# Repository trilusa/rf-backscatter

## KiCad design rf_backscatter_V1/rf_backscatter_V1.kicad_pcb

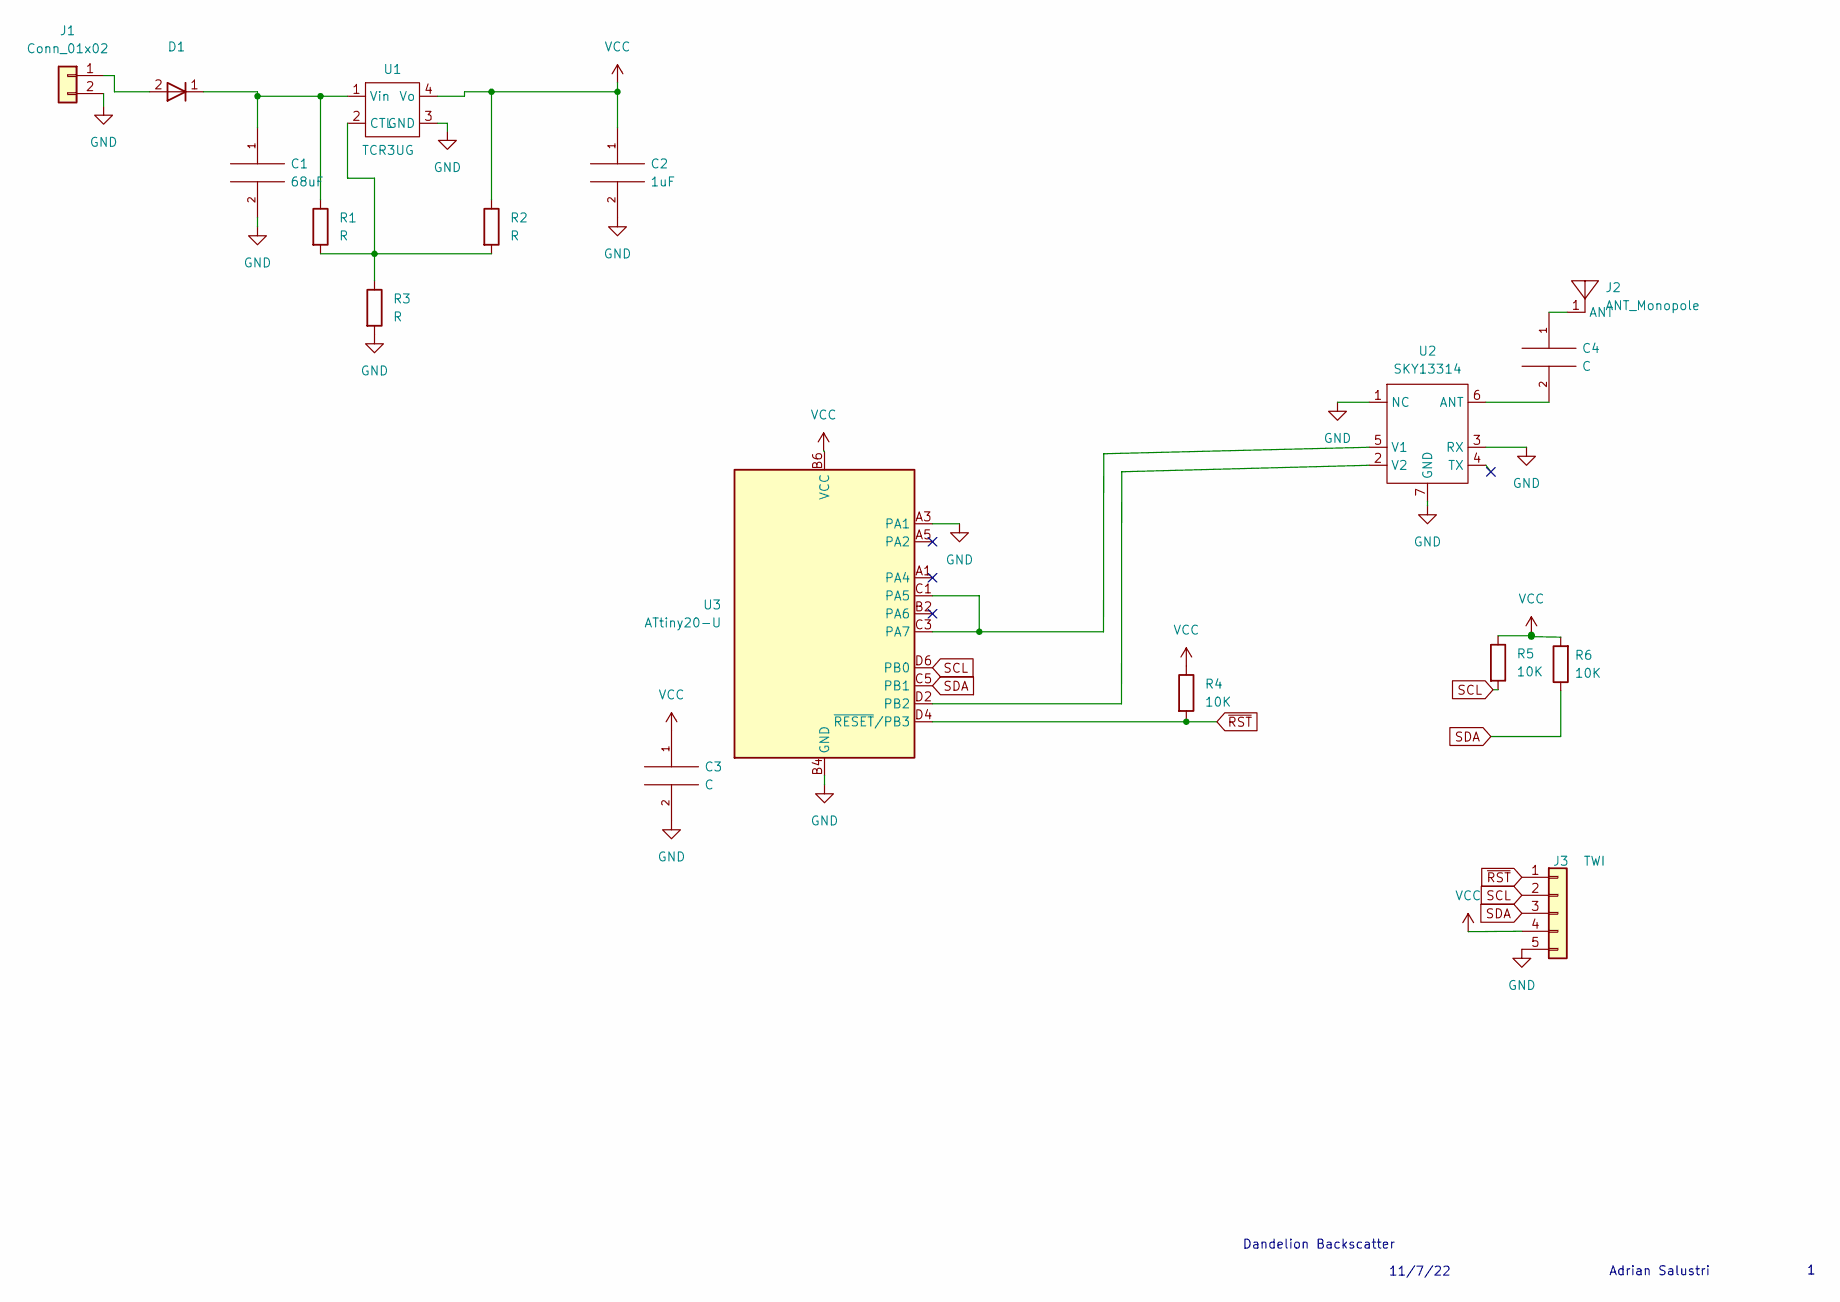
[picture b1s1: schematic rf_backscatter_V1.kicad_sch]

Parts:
C1: 68uF; C_0603_1608Metric_Pad1.08x0.95mm_HandSolder
C2: 1uF; C_0402_1005Metric_Pad0.74x0.62mm_HandSolder
C3, C4: C; C_0402_1005Metric_Pad0.74x0.62mm_HandSolder
D1: D; SOD882
J1: Conn_01x02; Dandelion_PVcell_connector
J2: ANT_Monopole; monopole_wire_antenna
J3: TWI; ATtiny20_TPI-I2C-HDR
R1, R2, R3: R; R_0402_1005Metric_Pad0.72x0.64mm_HandSolder
R4, R5, R6: 10K; R_0402_1005Metric
U1: TCR3UG
U2: SKY13314; SKY13314-374LF
U3: ATtiny20-U; WLCSP-12_1.403x1.555mm_P0.4mm_Stagger

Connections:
GND: C1.2, C2.2, C3.2, J1.2, J3.5, R3.2, U1.3 (GND), U2.1 (NC), U2.3 (RX), U2.7 (GND), U3.A3 (PA1), U3.B4 (GND)
unnamed: C1.1, D1.1 (K), R1.1, U1.1 (Vin)
unnamed: C4.1, J2.1 (ANT)
unnamed: C4.2, U2.6 (ANT)
unnamed: D1.2 (A), J1.1
unnamed: R1.2, R2.2, R3.1, U1.2 (CTL)
unnamed: U2.2 (V2), U3.D2 (PB2)
unnamed: U2.5 (V1), U3.C1 (PA5), U3.C3 (PA7)
SCL: J3.2, R5.2, U3.D6 (PB0)
SDA: J3.3, R6.1, U3.C5 (PB1)
VCC: C2.1, C3.1, J3.4, R2.1, R4.1, R5.1, R6.2, U1.4 (Vo), U3.B6 (VCC)
~RST: J3.1, R4.2, U3.D4 (~RESET/PB3)

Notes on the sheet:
Dandelion Backscatter
11/7/22
Adrian Salustri

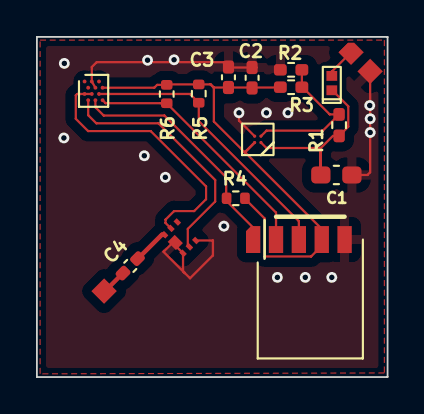
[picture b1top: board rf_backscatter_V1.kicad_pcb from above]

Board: 2 copper layers, 19.5 x 18.9 mm, 17 parts (0 on the bottom side), 12 nets.

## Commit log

2022-11-08 added V1 hardware
